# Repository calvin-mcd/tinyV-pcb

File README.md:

# tinyV-pcb

This is an integrated, hotswap pcb for the tinyV by BA (BAonDiscord7634). It is designed to be snapped in half at the mousebites in the middle of the pcb. a single 9pin jst cable will then connect the two halves.

## Layout

[Link](http://www.keyboard-layout-editor.com/#/gists/8b90b401f7d69f0f0c08135f7b12a323)

## Pictures

## Case

The case is being created by BA.

early design examples:

## Todo

- [ ] order & test pcb
- [ ] create firmware
- [ ] order & test case prototype

## Disclaimer

This PCB has been fully tested and confirmed to work. The members of the PCB development team are however not liable if you end up with a non-functional pcb. Order at your own risk. Support will not be provided but pull requests will be reviewed and possibly accepted.

## License

Shield: 

This work is licensed under a  
[Creative Commons Attribution-NonCommercial-ShareAlike 4.0 International License](http://creativecommons.org/licenses/by-nc-sa/4.0/).

## Credits

Any questions, contact BAonDiscord7634 & Calvin0563 on Discord.

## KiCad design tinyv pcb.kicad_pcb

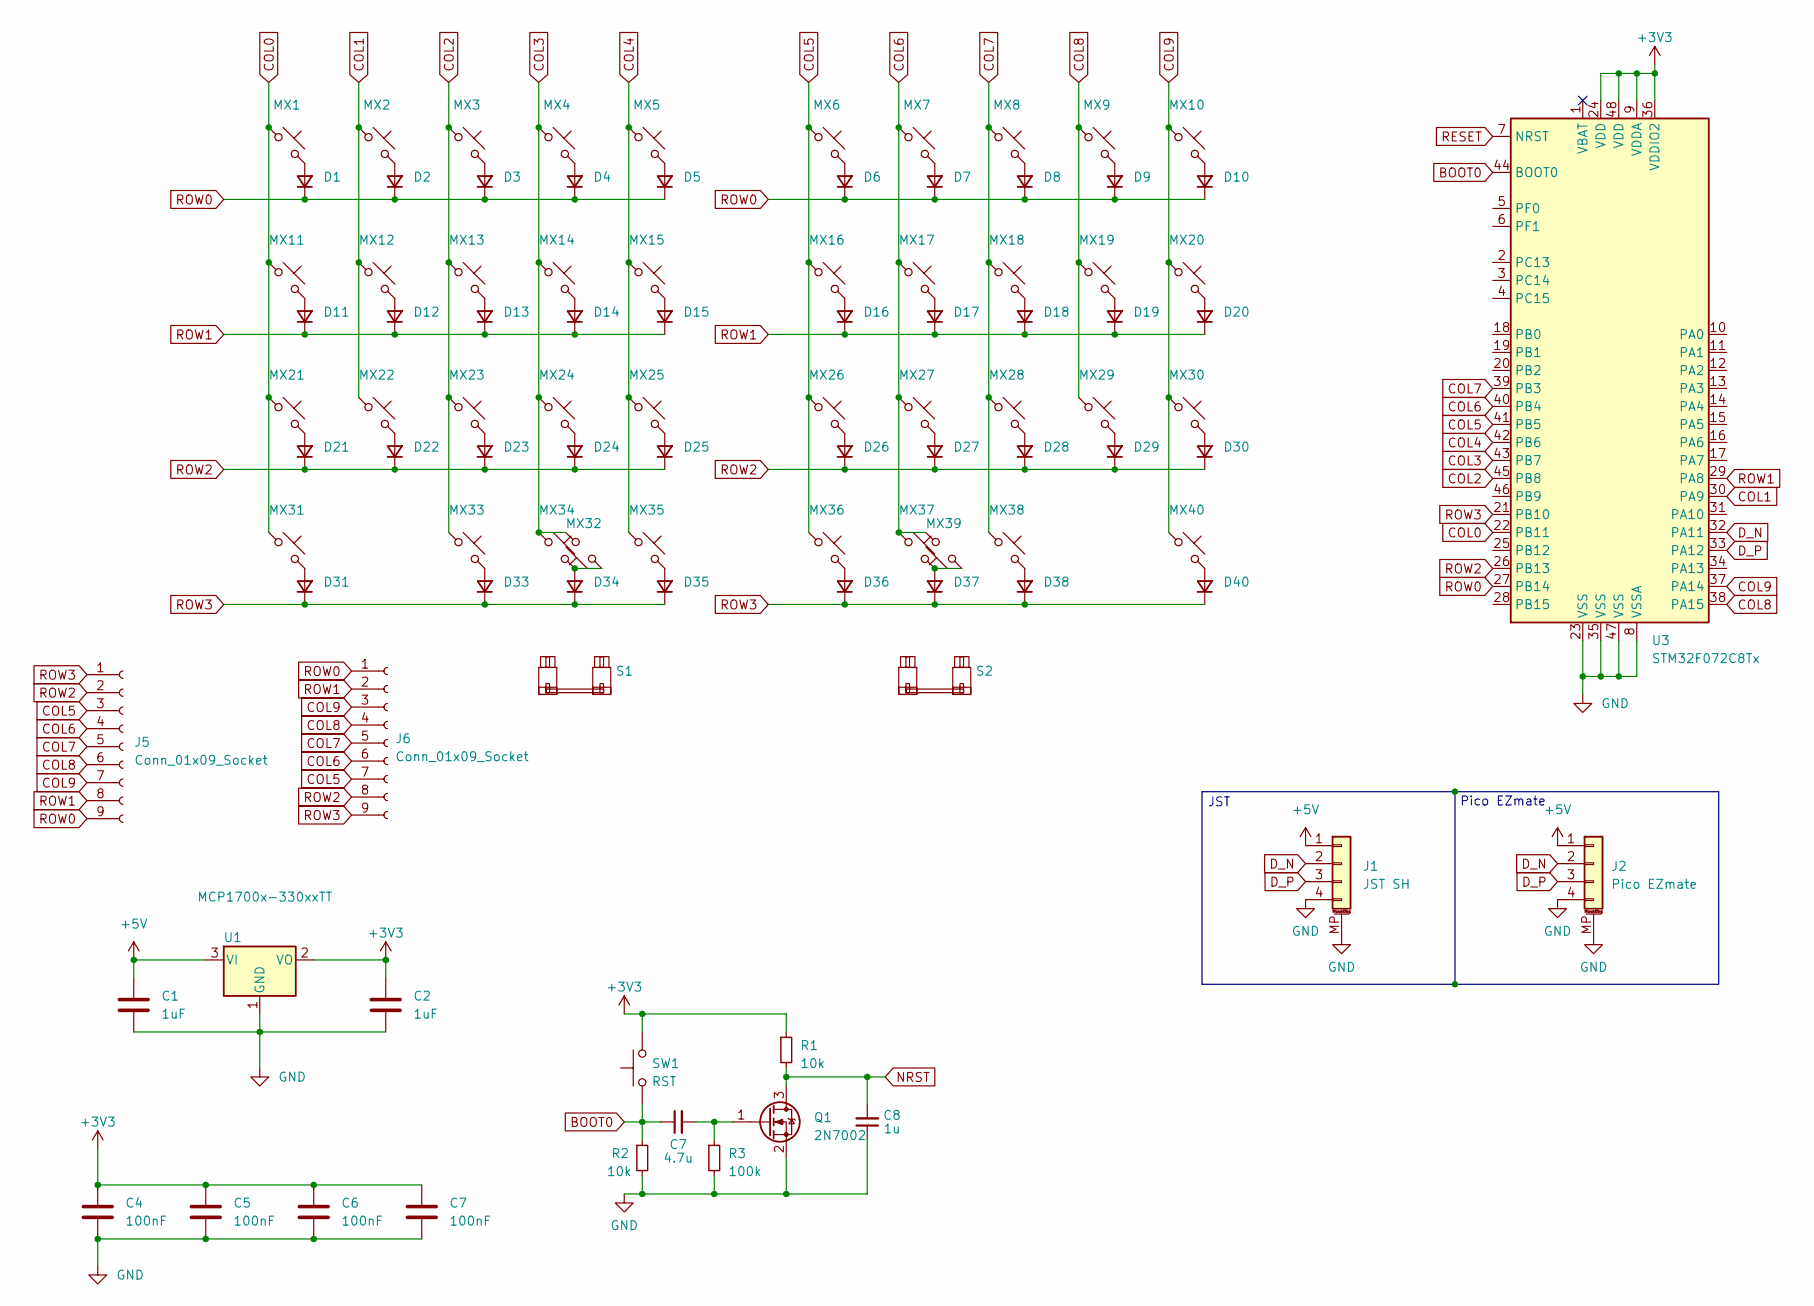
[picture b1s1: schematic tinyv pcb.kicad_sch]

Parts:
C1, C2: 1uF; C_0805_2012Metric; LCSC Part Number C28323
C4, C5, C6, C7: 100nF; C_0603_1608Metric; LCSC Part Number C14663
C8: 1u; C_0603_1608Metric
D1, D2, D3, D4, D5, D6, D7, D8, D9, D10, D11, D12, D13, D14, D15, D16, D17, D18, D19, D20, D21, D22, D23, D24, D25, D26, D27, D28, D29, D30, D31, D33, D34, D35, D36, D37, D38, D40: D_Small; D_SOD-123F
J1: JST SH; JST_SH_SM04B-SRSS-TB_1x04-1MP_P1.00mm_Horizontal
J2: Pico EZmate; Molex_Pico-EZmate_78171-0004_1x04-1MP_P1.20mm_Vertical
J5, J6: Conn_01x09_Socket; JST_SH_BM09B-SRSS-TB_1x09-1MP_P1.00mm_Vertical
MX1, MX2, MX3, MX4, MX5, MX6, MX7, MX8, MX9, MX10, MX11, MX12, MX13, MX14, MX15, MX16, MX17, MX18, MX19, MX20, MX21, MX22, MX23, MX24, MX25, MX26, MX27, MX28, MX29, MX30, MX31, MX32, MX33, MX34, MX35, MX36, MX37, MX38, MX39, MX40: MX_SW_HS; SW_MX_HS_1u
Q1: 2N7002; SOT-23
R1, R2: 10k; R_0603_1608Metric
R3: 100k; R_0603_1608Metric
S1, S2: MX_stab; STAB_MX_2u
SW1: RST; SW_SPST_SKQG_WithoutStem
U1: MCP1700x-330xxTT; SOT-23; LCSC Part Number C39051
U3: STM32F072C8Tx; LQFP-48_7x7mm_P0.5mm; LCSC Part Number C80488

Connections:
+5V: C1.1, J1.1, J2.1, U1.3 (VI); also elsewhere on the board
COL0: MX1.1, MX11.1, MX21.1, MX31.1, U1.22 (PB11)
COL1: MX2.1, MX12.1, MX22.1, U1.30 (PA9)
COL2: MX3.1, MX13.1, MX23.1, MX33.1, U1.45 (PB8)
COL3: MX4.1, MX14.1, MX24.1, MX32.2, MX34.1, U1.43 (PB7)
COL4: MX5.1, MX15.1, MX25.1, MX35.1, U1.42 (PB6)
COL5: J5.3, J6.7, MX6.1, MX16.1, MX26.1, MX36.1, U1.41 (PB5)
COL6: J5.4, J6.6, MX7.1, MX17.1, MX27.1, MX37.1, MX39.2, U1.40 (PB4)
COL7: J5.5, J6.5, MX8.1, MX18.1, MX28.1, MX38.1, U1.39 (PB3)
COL8: J5.6, J6.4, MX9.1, MX19.1, MX29.1, U1.38 (PA15)
COL9: J5.7, J6.3, MX10.1, MX20.1, MX30.1, MX40.1, U1.37 (PA14)
D_N: J1.2, J2.2, U1.32 (PA11)
D_P: J1.3, J2.3, U1.33 (PA12)
NRST: C8.2, Q1.3 (D), R1.2
unnamed: D1.2 (A), MX1.2
unnamed: D2.2 (A), MX2.2
unnamed: D3.2 (A), MX3.2
unnamed: D4.2 (A), MX4.2
unnamed: D5.2 (A), MX5.2
unnamed: D6.2 (A), MX6.2
unnamed: D7.2 (A), MX7.2
unnamed: D8.2 (A), MX8.2
unnamed: D9.2 (A), MX9.2
unnamed: D10.2 (A), MX10.2
unnamed: D11.2 (A), MX11.2
unnamed: D12.2 (A), MX12.2
unnamed: D13.2 (A), MX13.2
unnamed: D14.2 (A), MX14.2
unnamed: D15.2 (A), MX15.2
unnamed: D16.2 (A), MX16.2
unnamed: D17.2 (A), MX17.2
unnamed: D18.2 (A), MX18.2
unnamed: D19.2 (A), MX19.2
unnamed: D20.2 (A), MX20.2
unnamed: D21.2 (A), MX21.2
unnamed: D22.2 (A), MX22.2
unnamed: D23.2 (A), MX23.2
unnamed: D24.2 (A), MX24.2
unnamed: D25.2 (A), MX25.2
unnamed: D26.2 (A), MX26.2
unnamed: D27.2 (A), MX27.2
unnamed: D28.2 (A), MX28.2
unnamed: D29.2 (A), MX29.2
unnamed: D30.2 (A), MX30.2
unnamed: D31.2 (A), MX31.2
unnamed: D33.2 (A), MX33.2
unnamed: D34.2 (A), MX32.1, MX34.2
unnamed: D35.2 (A), MX35.2
unnamed: D36.2 (A), MX36.2
unnamed: D37.2 (A), MX37.2, MX39.1
unnamed: D38.2 (A), MX38.2
unnamed: D40.2 (A), MX40.2
RESET: U1.7 (NRST)
ROW0: D1.1 (K), D2.1 (K), D3.1 (K), D4.1 (K), D5.1 (K), D6.1 (K), D7.1 (K), D8.1 (K), D9.1 (K), D10.1 (K), J5.9, J6.1, U1.27 (PB14)
ROW1: D11.1 (K), D12.1 (K), D13.1 (K), D14.1 (K), D15.1 (K), D16.1 (K), D17.1 (K), D18.1 (K), D19.1 (K), D20.1 (K), J5.8, J6.2, U1.29 (PA8)
ROW2: D21.1 (K), D22.1 (K), D23.1 (K), D24.1 (K), D25.1 (K), D26.1 (K), D27.1 (K), D28.1 (K), D29.1 (K), D30.1 (K), J5.2, J6.8, U1.26 (PB13)
ROW3: D31.1 (K), D33.1 (K), D34.1 (K), D35.1 (K), D36.1 (K), D37.1 (K), D38.1 (K), D40.1 (K), J5.1, J6.9, U1.21 (PB10)

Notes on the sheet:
Pico EZmate
JST

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
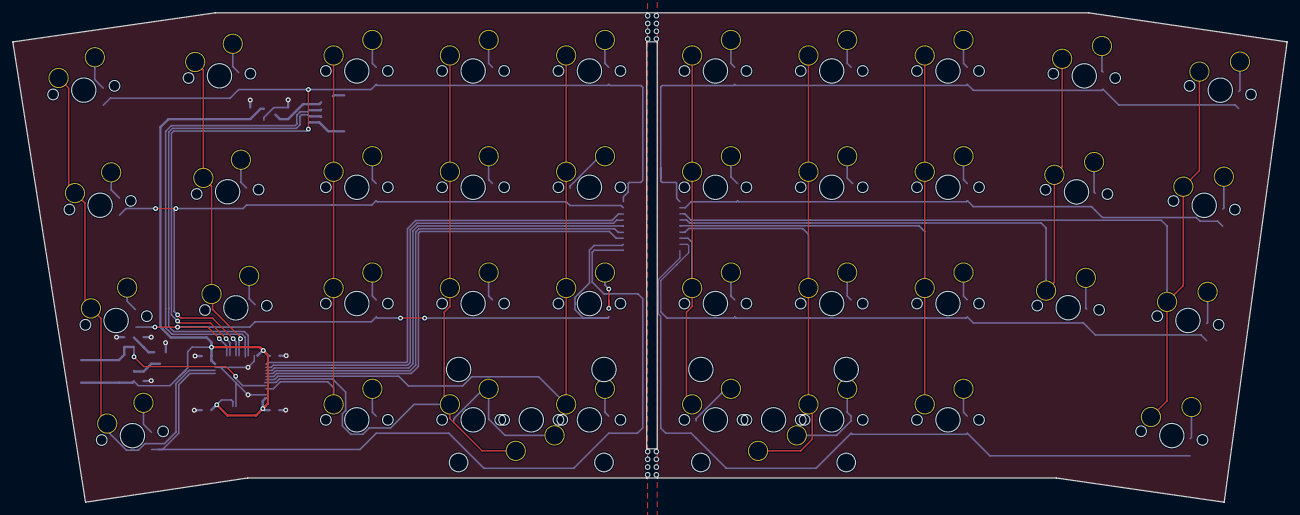
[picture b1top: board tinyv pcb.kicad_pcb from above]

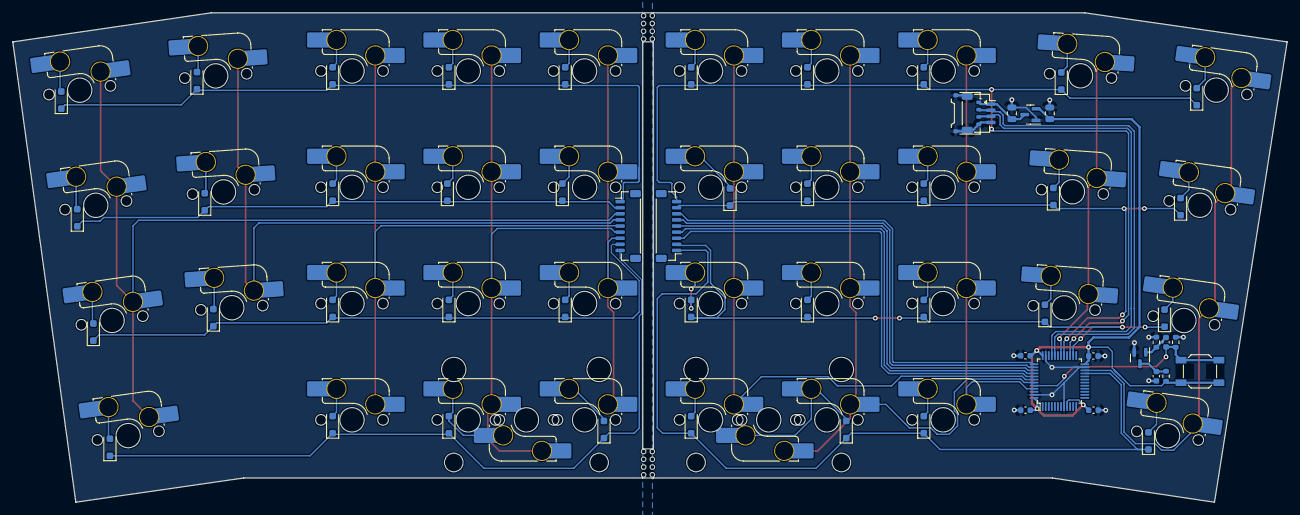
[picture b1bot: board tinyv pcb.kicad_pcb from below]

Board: 2 copper layers, 208.8 x 80.2 mm, 99 parts (97 on the bottom side), 60 nets.

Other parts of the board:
C3: 100nF; C_0603_1608Metric
U2: MCP1700x-330xxTT; SOT-23

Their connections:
+5V: U2.3 (VI); also elsewhere on the board

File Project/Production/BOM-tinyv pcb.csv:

Comment,Designator,Footprint,LCSC
1uF,"C1,C2,C8",C_0603_1608Metric,C106215
Conn_01x09_Socket,"J5,J6",JST_SH_SM09B-SRSS-TB_1x09-1MP_P1.00mm_Horizontal,C160408
100nF,"C10,C3,C4,C5,C9",C_0603_1608Metric,C2930551
RST,SW1,SW_SPST_SKQG_WithoutStem,C318884
MCP1700x-330xxTT,U2,SOT-23,C39051
100k,R3,R_0603_1608Metric,C4107493
MX_SW_HS,"MX1,MX10,MX11,MX12,MX13,MX14,MX15,MX16,MX17,MX18,MX19,MX2,MX20,MX21,MX22,MX23,MX24,MX25,MX26,MX27,MX28,MX29,MX3,MX30,MX31,MX32,MX33,MX34,MX35,MX36,MX37,MX38,MX39,MX4,MX40,MX5,MX6,MX7,MX8,MX9",SW_MX_HS_1u,C5156480
Pico EZmate,J2,Molex_Pico-EZmate_78171-0004_1x04-1MP_P1.20mm_Vertical,C588524
10uF,C11,C_0603_1608Metric,C596327
D_Small,"D1,D10,D11,D12,D13,D14,D15,D16,D17,D18,D19,D2,D20,D21,D22,D23,D24,D25,D26,D27,D28,D29,D3,D30,D31,D33,D34,D35,D36,D37,D38,D4,D40,D5,D6,D7,D8,D9",D_SOD-123F,C64898
4.7uF,C7,C_0603_1608Metric,C695178
STM32F072C8Tx,U1,LQFP-48_7x7mm_P0.5mm,C80488
2N7002,Q1,SOT-23,C8545
10k,"R1,R2",R_0603_1608Metric,C859115

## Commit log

2023-08-16 routing improvements, error check, cleanup
2023-08-20 production files & bom, pos missing
2023-08-24 slight routing change, necessary?
2023-08-29 production files created
    not yet finished
2023-09-12 update project
2023-09-14 backup
2023-12-16 added a version that uses FFC instead of JST
2024-02-23 fresh gerbers
